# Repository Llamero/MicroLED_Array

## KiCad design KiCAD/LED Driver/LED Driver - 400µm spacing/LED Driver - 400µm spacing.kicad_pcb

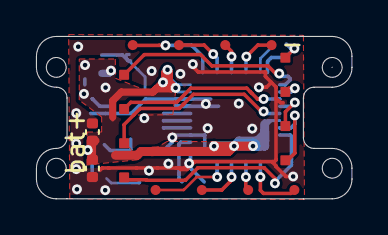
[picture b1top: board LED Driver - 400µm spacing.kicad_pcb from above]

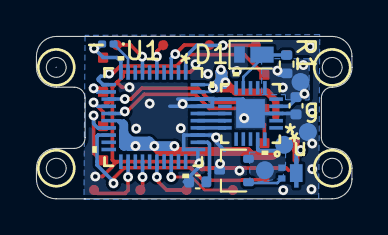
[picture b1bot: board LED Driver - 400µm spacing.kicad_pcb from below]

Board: 2 copper layers, 17.5 x 9.0 mm, 17 parts (15 on the bottom side), 12 nets.

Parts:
BT1: LiPo Cell; LPM0940
C1, C2, C3, C4: 1µF; C_0402_1005Metric
D1: D_Photo; DIO_VEMD4110X01
D2: LED; LED_0201_0603Metric
H1, H2, H3, H4: MountingHole; M1 hole
Q1: Q_NMOS_GSD; SOT-323_SC-70 - thin
R1: 1M; R_0402_1005Metric
TP2: UPDI Pogo Pads; 1mm pad x4
U1: LP5868TRKPR; VQFN40-RKP_TEX
U2: ATtiny3226
U3: XC61GC3002HR-G; XC61G_USP-3_TOR

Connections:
+BATT: C1.1, C3.2, C4.2, R1.1, TP2.3, U1.16 (VLED), U1.39 (VIO_EN), U1.40 (VCC), U2.4 (Vcc), U3.3 (VIN)
-BATT: Q1.2 (S), TP2.4, U3.1 (VSS)
/Col1: D2.2 (A), U1.10 (SW0)
/Photodiode: D1.1 (K), R1.2, U2.9 (4/PB5)
/SCL: U1.35 (SCL_SCK), U2.14 (PB0/9~)
/SDA: U1.36 (SDA_MOSI), U2.13 (8~/PB1)
/UPDI: TP2.2, U2.19 (PA0/17)
/Vsync: U1.34 (VSYNC), U2.15 (PC0/10)
GND: C1.2, C2.2, C3.1, C4.1, D1.2 (A), Q1.3 (D), TP2.1, U1.31 (AGND), U1.33 (IFS), U1.37 (ADDR0_MISO), U1.38 (ADDR1_SS), U2.3 (Gnd), U2.11 (6/PB3), U2.21 (Epad)
unnamed: D2.1 (K), U1.9 (CS8)
unnamed: Q1.1 (G), U3.2 (VOUT)
unnamed: C2.1, U1.32 (VCAP)

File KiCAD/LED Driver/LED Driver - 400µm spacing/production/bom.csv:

Designator,Footprint,Quantity,Value,LCSC Part #
BT1,LPM0940,1,LiPo Cell,
"C1, C2, C3, C4",0402,4,1µF,
D1,DIO_VEMD4110X01,1,D_Photo,
D2,0201,1,LED,
Q1,SOT-323_SC-70 - thin,1,Q_NMOS_GSD,
R1,0402,1,1M,
TP2,1mm pad x4,1,UPDI Pogo Pads,
U1,VQFN40-RKP_TEX,1,LP5868TRKPR,
U2,ATtiny3226,1,ATtiny3226,
U3,XC61G_USP-3_TOR,1,XC61GC3002HR-G,

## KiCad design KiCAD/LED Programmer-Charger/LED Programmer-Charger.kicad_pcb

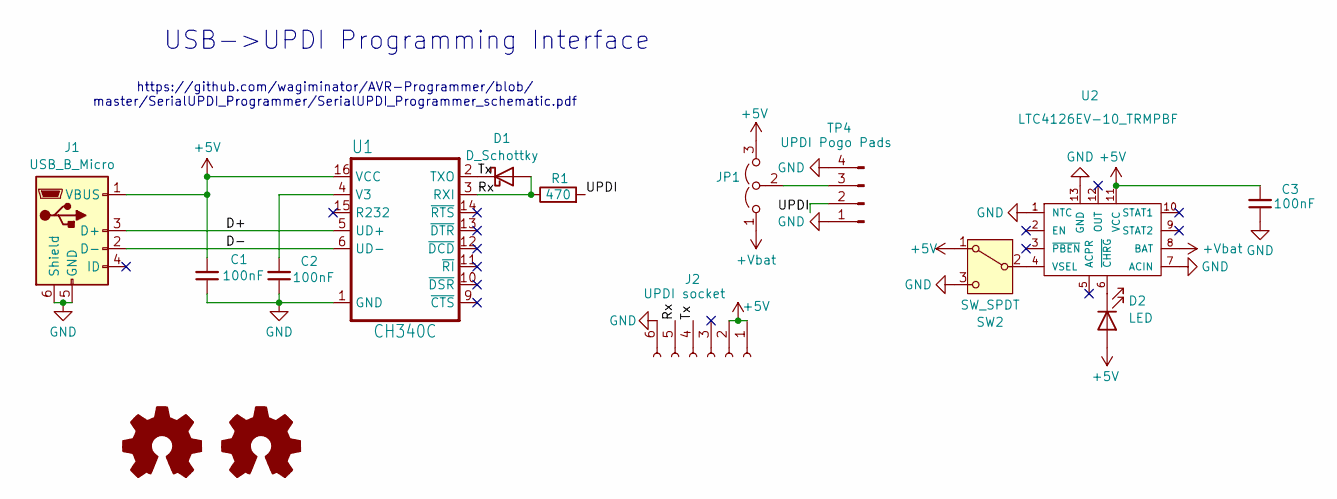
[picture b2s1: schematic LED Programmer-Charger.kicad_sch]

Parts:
C1, C2, C3: 100nF; C_0805_2012Metric; Part MT21B104K500CT
D1: D_Schottky; D_SOD-323; Part CUS10S30,H3F
D2: LED; LED_0603_1608Metric; Part LTST-C170KRKT
J1: USB_B_Micro; CUI_UJ2-MIBH-G-SMT-TR; Part UJ2-MIBH-G-SMT-TR
J2: UPDI socket; PinSocket_1x06_P2.54mm_Vertical_SMD_Pin1Right; Part NPTC061KFXC-RC
JP1: Jumper_3_Open; SolderJumper-3_P2.0mm_Open_TrianglePad1.0x1.5mm
R1: 470; R_0805_2012Metric; Part RP0805FRE07470RL
SW2: SW_SPDT; CL-SB-12B-01_NDC; Part CL-SB-12B-01T
SYM1: Logo_Open_Hardware_Small; CC-BY-SA Symbol
SYM2: Logo_Open_Hardware_Small; OSHW-Logo_5.7x6mm_SilkScreen
TP4: UPDI Pogo Pads; 1mm pad x4; Part 0985-0-15-20-71-14-11-0
U1: CH340C; SOP-16_3.9x9.9mm_P1.27mm; Part B0BK991VVV
U2: LTC4126EV-10_TRMPBF; LTC4126-10; Part LTC4126EV-10#TRMPBF

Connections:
+5V: C1.2, C3.2, D2.2 (A), J1.1 (VBUS), J2.1, J2.2, JP1.3 (B), SW2.1 (A), U1.16 (VCC), U2.11 (VCC)
+Vbat: JP1.1 (A), U2.8 (BAT)
/D+: J1.3 (D+), U1.5 (UD+)
/D-: J1.2 (D-), U1.6 (UD-)
/Rx: D1.2 (A), J2.5, R1.1, U1.3 (RXI)
/Tx: D1.1 (K), J2.4, U1.2 (TXO)
/UPDI: R1.2, TP4.2
GND: C1.1, C2.1, C3.1, J1.5 (GND), J1.6 (Shield), J2.6, SW2.3 (C), TP4.1, TP4.4, U1.1 (GND), U2.1 (NTC), U2.7 (ACIN), U2.13 (GND)
unnamed: D2.1 (K), U2.6 (~CHRG)
unnamed: JP1.2 (C), TP4.3
unnamed: SW2.2 (B), U2.4 (VSEL)
unnamed: C2.2, U1.4 (V3)

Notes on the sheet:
USB->UPDI Programming Interface
https://github.com/wagiminator/AVR-Programmer/blob/ master/SerialUPDI_Programmer/SerialUPDI_Programmer_schematic.pdf

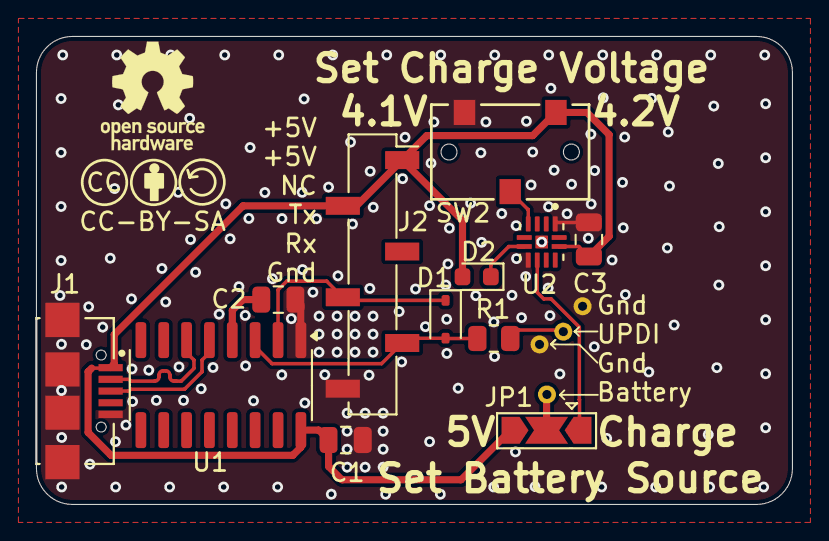
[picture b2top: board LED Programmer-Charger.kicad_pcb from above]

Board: 2 copper layers, 42.0 x 26.0 mm, 15 parts (0 on the bottom side), 12 nets.

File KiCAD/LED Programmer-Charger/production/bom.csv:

Designator,Footprint,Quantity,Value,LCSC Part #
"C1, C2, C3",0805,3,100nF,
D1,D_SOD-323,1,D_Schottky,
D2,0603,1,LED,
J1,CUI_UJ2-MIBH-G-SMT-TR,1,USB_B_Micro,
J2,PinSocket_1x06_P2.54mm_Vertical_SMD_Pin1Right,1,UPDI socket,
R1,0805,1,470,
SW2,CL-SB-12B-01_NDC,1,SW_SPDT,
TP4,1mm pad x4,1,UPDI Pogo Pads,
U1,SOP-16_3.9x9.9mm_P1.27mm,1,CH340C,
U2,LTC4126-10,1,LTC4126EV-10_TRMPBF,

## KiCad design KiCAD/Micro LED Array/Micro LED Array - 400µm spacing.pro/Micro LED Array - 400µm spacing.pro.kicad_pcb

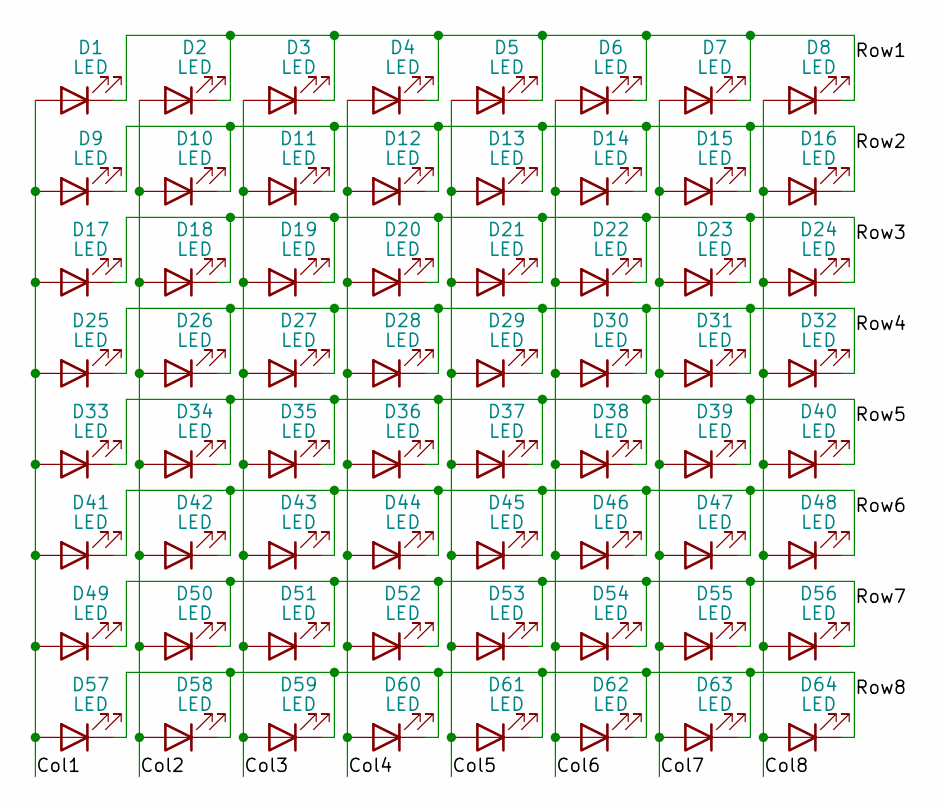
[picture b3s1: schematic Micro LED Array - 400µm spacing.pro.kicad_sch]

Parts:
D1, D2, D3, D4, D5, D6, D7, D8, D9, D10, D11, D12, D13, D14, D15, D16, D17, D18, D19, D20, D21, D22, D23, D24, D25, D26, D27, D28, D29, D30, D31, D32, D33, D34, D35, D36, D37, D38, D39, D40, D41, D42, D43, D44, D45, D46, D47, D48, D49, D50, D51, D52, D53, D54, D55, D56, D57, D58, D59, D60, D61, D62, D63, D64: LED; LED_APG0603SEC-E-TT_KNB - with via; Part LTST-FC03AD-5A

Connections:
/Col1: D1.2 (A), D9.2 (A), D17.2 (A), D25.2 (A), D33.2 (A), D41.2 (A), D49.2 (A), D57.2 (A)
/Col2: D2.2 (A), D10.2 (A), D18.2 (A), D26.2 (A), D34.2 (A), D42.2 (A), D50.2 (A), D58.2 (A)
/Col3: D3.2 (A), D11.2 (A), D19.2 (A), D27.2 (A), D35.2 (A), D43.2 (A), D51.2 (A), D59.2 (A)
/Col4: D4.2 (A), D12.2 (A), D20.2 (A), D28.2 (A), D36.2 (A), D44.2 (A), D52.2 (A), D60.2 (A)
/Col5: D5.2 (A), D13.2 (A), D21.2 (A), D29.2 (A), D37.2 (A), D45.2 (A), D53.2 (A), D61.2 (A)
/Col6: D6.2 (A), D14.2 (A), D22.2 (A), D30.2 (A), D38.2 (A), D46.2 (A), D54.2 (A), D62.2 (A)
/Col7: D7.2 (A), D15.2 (A), D23.2 (A), D31.2 (A), D39.2 (A), D47.2 (A), D55.2 (A), D63.2 (A)
/Col8: D8.2 (A), D16.2 (A), D24.2 (A), D32.2 (A), D40.2 (A), D48.2 (A), D56.2 (A), D64.2 (A)
/Row1: D1.1 (K), D2.1 (K), D3.1 (K), D4.1 (K), D5.1 (K), D6.1 (K), D7.1 (K), D8.1 (K)
/Row2: D9.1 (K), D10.1 (K), D11.1 (K), D12.1 (K), D13.1 (K), D14.1 (K), D15.1 (K), D16.1 (K)
/Row3: D17.1 (K), D18.1 (K), D19.1 (K), D20.1 (K), D21.1 (K), D22.1 (K), D23.1 (K), D24.1 (K)
/Row4: D25.1 (K), D26.1 (K), D27.1 (K), D28.1 (K), D29.1 (K), D30.1 (K), D31.1 (K), D32.1 (K)
/Row5: D33.1 (K), D34.1 (K), D35.1 (K), D36.1 (K), D37.1 (K), D38.1 (K), D39.1 (K), D40.1 (K)
/Row6: D41.1 (K), D42.1 (K), D43.1 (K), D44.1 (K), D45.1 (K), D46.1 (K), D47.1 (K), D48.1 (K)
/Row7: D49.1 (K), D50.1 (K), D51.1 (K), D52.1 (K), D53.1 (K), D54.1 (K), D55.1 (K), D56.1 (K)
/Row8: D57.1 (K), D58.1 (K), D59.1 (K), D60.1 (K), D61.1 (K), D62.1 (K), D63.1 (K), D64.1 (K)

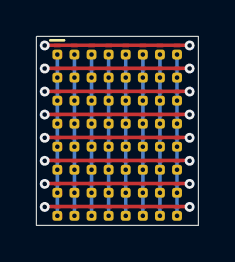
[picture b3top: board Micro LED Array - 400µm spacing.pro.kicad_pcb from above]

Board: 2 copper layers, 9.0 x 10.5 mm, 64 parts (0 on the bottom side), 16 nets.

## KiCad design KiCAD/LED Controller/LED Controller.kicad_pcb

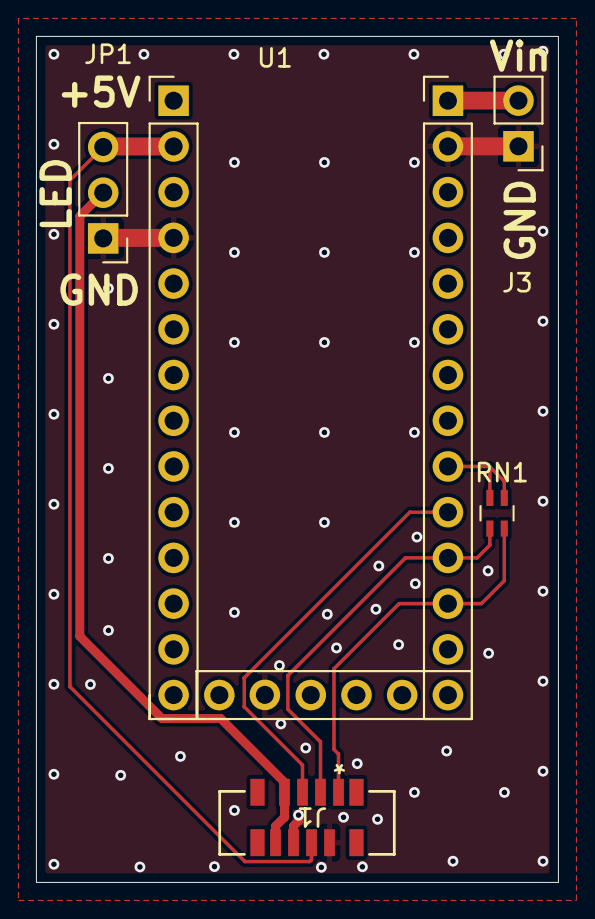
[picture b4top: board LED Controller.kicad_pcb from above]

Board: 2 copper layers, 29.0 x 47.0 mm, 5 parts (0 on the bottom side), 8 nets.

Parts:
J1: 0525590870; CON_525590870_MOL - 8x ribbon vert
J3: Conn_01x02_Pin; PinHeader_1x02_P2.54mm_Vertical
JP1: Jumper_3_Open; PinHeader_1x03_P2.54mm_Vertical
RN1: R_Pack02; R_Array_Concave_2x0603
U1: Itsy_Bitsy_32u4; Itsy Bitsy 32u4

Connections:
+5V: J1.4, JP1.3 (B), U1.2 (5V)
/12V: J3.2, U1.33 (VBat)
/SCL: J1.3, RN1.3 (R2.2), U1.23 (~3_SCL)
/SDA: J1.1, RN1.4 (R1.2), U1.22 (2_SDA)
/VLED: J1.7, J1.8, JP1.2 (C)
/Vsync: J1.5, U1.24 (~5)
GND: J1.2, J1.6, J3.1, JP1.1 (A), U1.4 (GND), U1.16 (Gnd), U1.32 (Gnd)
unnamed: RN1.1 (R1.1), RN1.2 (R2.1), U1.25 (7)

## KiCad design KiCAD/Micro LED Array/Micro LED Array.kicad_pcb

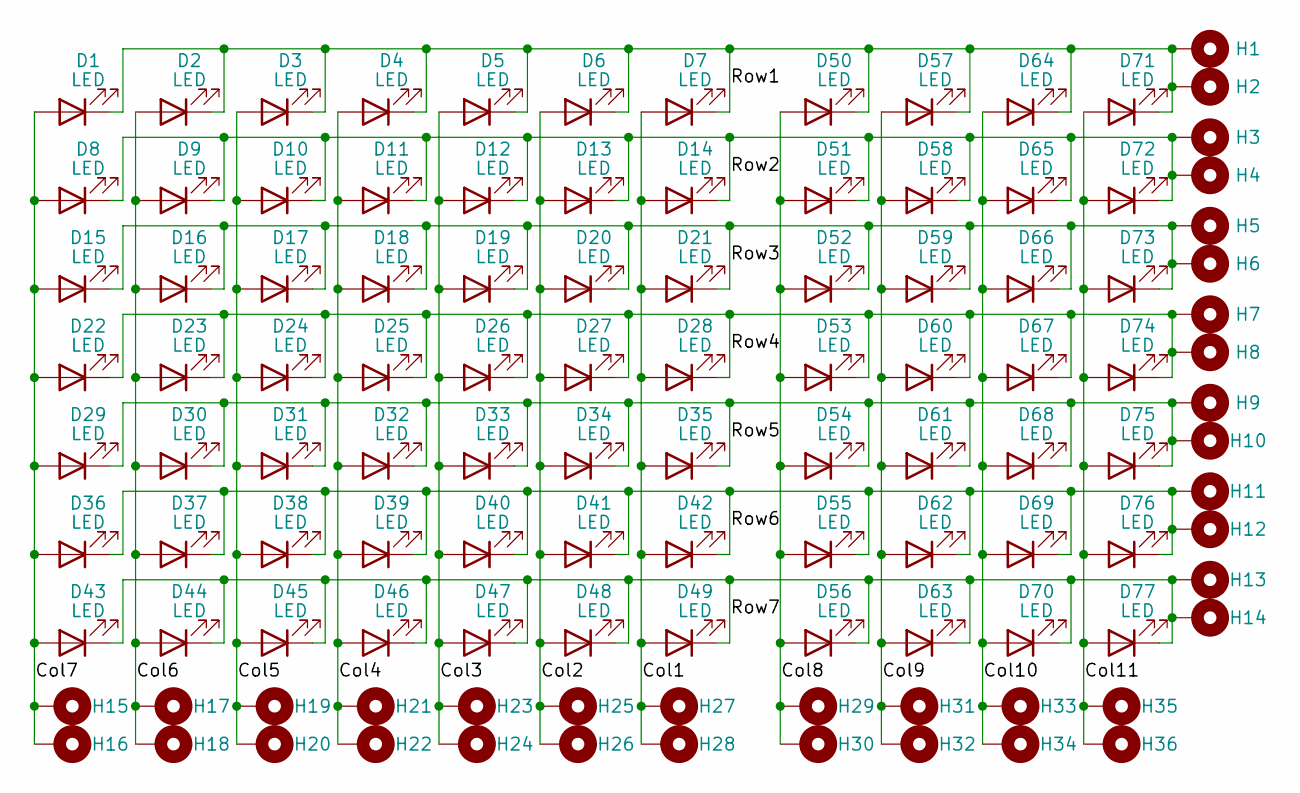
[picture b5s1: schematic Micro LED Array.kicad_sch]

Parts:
D1, D2, D3, D4, D5, D6, D7, D8, D9, D10, D11, D12, D13, D14, D15, D16, D17, D18, D19, D20, D21, D22, D23, D24, D25, D26, D27, D28, D29, D30, D31, D32, D33, D34, D35, D36, D37, D38, D39, D40, D41, D42, D43, D44, D45, D46, D47, D48, D49, D50, D51, D52, D53, D54, D55, D56, D57, D58, D59, D60, D61, D62, D63, D64, D65, D66, D67, D68, D69, D70, D71, D72, D73, D74, D75, D76, D77: LED; LED_APG0603SEC-E-TT_KNB - with via; Part APG0603SEC-E-TT
H1, H2, H3, H4, H5, H6, H7, H8, H9, H10, H11, H12, H13, H14, H15, H16, H17, H18, H19, H20, H21, H22, H23, H24, H25, H26, H27, H28, H29, H30, H31, H32, H33, H34, H35, H36: Via Pad; Column Via

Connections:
/Col1: D7.2 (A), D14.2 (A), D21.2 (A), D28.2 (A), D35.2 (A), D42.2 (A), D49.2 (A), H27.1, H28.1
/Col2: D6.2 (A), D13.2 (A), D20.2 (A), D27.2 (A), D34.2 (A), D41.2 (A), D48.2 (A), H25.1, H26.1
/Col3: D5.2 (A), D12.2 (A), D19.2 (A), D26.2 (A), D33.2 (A), D40.2 (A), D47.2 (A), H23.1, H24.1
/Col4: D4.2 (A), D11.2 (A), D18.2 (A), D25.2 (A), D32.2 (A), D39.2 (A), D46.2 (A), H21.1, H22.1
/Col5: D3.2 (A), D10.2 (A), D17.2 (A), D24.2 (A), D31.2 (A), D38.2 (A), D45.2 (A), H19.1, H20.1
/Col6: D2.2 (A), D9.2 (A), D16.2 (A), D23.2 (A), D30.2 (A), D37.2 (A), D44.2 (A), H17.1, H18.1
/Col7: D1.2 (A), D8.2 (A), D15.2 (A), D22.2 (A), D29.2 (A), D36.2 (A), D43.2 (A), H15.1, H16.1
/Col8: D50.2 (A), D51.2 (A), D52.2 (A), D53.2 (A), D54.2 (A), D55.2 (A), D56.2 (A), H29.1, H30.1
/Col9: D57.2 (A), D58.2 (A), D59.2 (A), D60.2 (A), D61.2 (A), D62.2 (A), D63.2 (A), H31.1, H32.1
/Col10: D64.2 (A), D65.2 (A), D66.2 (A), D67.2 (A), D68.2 (A), D69.2 (A), D70.2 (A), H33.1, H34.1
/Col11: D71.2 (A), D72.2 (A), D73.2 (A), D74.2 (A), D75.2 (A), D76.2 (A), D77.2 (A), H35.1, H36.1
/Row1: D1.1 (K), D2.1 (K), D3.1 (K), D4.1 (K), D5.1 (K), D6.1 (K), D7.1 (K), D50.1 (K), D57.1 (K), D64.1 (K), D71.1 (K), H1.1, H2.1
/Row2: D8.1 (K), D9.1 (K), D10.1 (K), D11.1 (K), D12.1 (K), D13.1 (K), D14.1 (K), D51.1 (K), D58.1 (K), D65.1 (K), D72.1 (K), H3.1, H4.1
/Row3: D15.1 (K), D16.1 (K), D17.1 (K), D18.1 (K), D19.1 (K), D20.1 (K), D21.1 (K), D52.1 (K), D59.1 (K), D66.1 (K), D73.1 (K), H5.1, H6.1
/Row4: D22.1 (K), D23.1 (K), D24.1 (K), D25.1 (K), D26.1 (K), D27.1 (K), D28.1 (K), D53.1 (K), D60.1 (K), D67.1 (K), D74.1 (K), H7.1, H8.1
/Row5: D29.1 (K), D30.1 (K), D31.1 (K), D32.1 (K), D33.1 (K), D34.1 (K), D35.1 (K), D54.1 (K), D61.1 (K), D68.1 (K), D75.1 (K), H9.1, H10.1
/Row6: D36.1 (K), D37.1 (K), D38.1 (K), D39.1 (K), D40.1 (K), D41.1 (K), D42.1 (K), D55.1 (K), D62.1 (K), D69.1 (K), D76.1 (K), H11.1, H12.1
/Row7: D43.1 (K), D44.1 (K), D45.1 (K), D46.1 (K), D47.1 (K), D48.1 (K), D49.1 (K), D56.1 (K), D63.1 (K), D70.1 (K), D77.1 (K), H13.1, H14.1

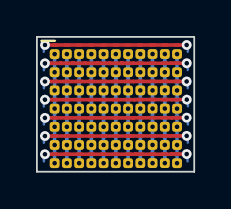
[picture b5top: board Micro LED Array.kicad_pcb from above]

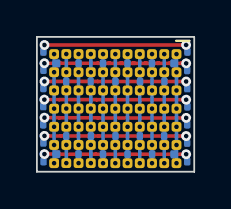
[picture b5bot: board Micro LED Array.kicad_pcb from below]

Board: 2 copper layers, 8.7 x 7.5 mm, 113 parts (36 on the bottom side), 18 nets.

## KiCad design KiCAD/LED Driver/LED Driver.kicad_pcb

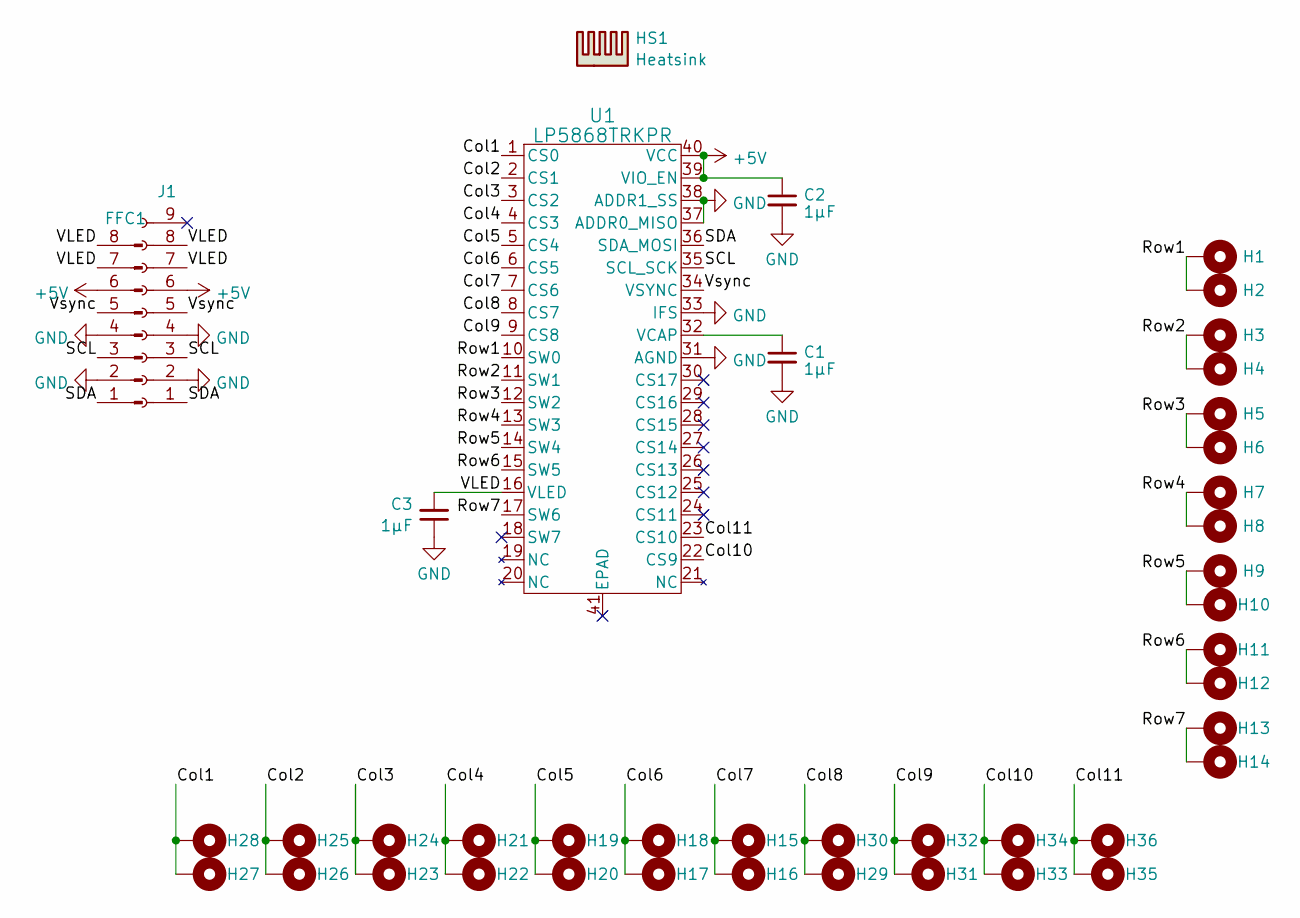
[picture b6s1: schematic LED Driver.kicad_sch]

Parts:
C1, C2, C3: 1µF; C_0402_1005Metric; Part CL05A105KA5NQNC
FFC1: FFC; Part 0151660093
H1, H2, H3, H4, H5, H6, H7, H8, H9, H10, H11, H12, H13, H14, H15, H16, H17, H18, H19, H20, H21, H22, H23, H24, H25, H26, H27, H28, H29, H30, H31, H32, H33, H34, H35, H36: Via Pad; Column Via
HS1: Heatsink; heatsink; Part V2016B
J1: 0525590870; CON_525590870_MOL - 8x ribbon vert; Part 0525590870
U1: LP5868TRKPR; VQFN40-RKP_TEX; Part LP5868TRKPR

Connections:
+5V: C2.1, FFC1.6, J1.6, U1.39 (VIO_EN), U1.40 (VCC)
/Col1: H27.1, H28.1, U1.1 (CS0)
/Col2: H25.1, H26.1, U1.2 (CS1)
/Col3: H23.1, H24.1, U1.3 (CS2)
/Col4: H21.1, H22.1, U1.4 (CS3)
/Col5: H19.1, H20.1, U1.5 (CS4)
/Col6: H17.1, H18.1, U1.6 (CS5)
/Col7: H15.1, H16.1, U1.7 (CS6)
/Col8: H29.1, H30.1, U1.8 (CS7)
/Col9: H31.1, H32.1, U1.9 (CS8)
/Col10: H33.1, H34.1, U1.22 (CS9)
/Col11: H35.1, H36.1, U1.23 (CS10)
/Row1: H1.1, H2.1, U1.10 (SW0)
/Row2: H3.1, H4.1, U1.11 (SW1)
/Row3: H5.1, H6.1, U1.12 (SW2)
/Row4: H7.1, H8.1, U1.13 (SW3)
/Row5: H9.1, H10.1, U1.14 (SW4)
/Row6: H11.1, H12.1, U1.15 (SW5)
/Row7: H13.1, H14.1, U1.17 (SW6)
/SCL: FFC1.3, J1.3, U1.35 (SCL_SCK)
/SDA: FFC1.1, J1.1, U1.36 (SDA_MOSI)
/VLED: C3.2, FFC1.7, FFC1.8, J1.7, J1.8, U1.16 (VLED)
/Vsync: FFC1.5, J1.5, U1.34 (VSYNC)
GND: C1.2, C2.2, C3.1, FFC1.2, FFC1.4, J1.2, J1.4, U1.31 (AGND), U1.33 (IFS), U1.37 (ADDR0_MISO), U1.38 (ADDR1_SS)
unnamed: C1.1, U1.32 (VCAP)

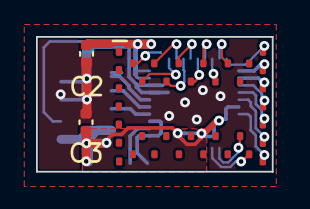
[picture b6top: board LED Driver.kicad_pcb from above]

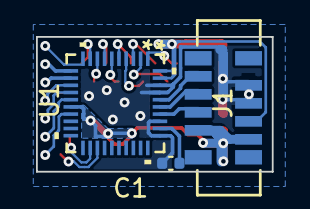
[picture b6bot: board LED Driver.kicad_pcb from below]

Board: 2 copper layers, 13.1 x 7.5 mm, 42 parts (4 on the bottom side), 25 nets.

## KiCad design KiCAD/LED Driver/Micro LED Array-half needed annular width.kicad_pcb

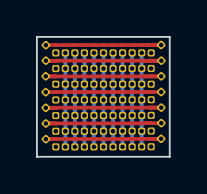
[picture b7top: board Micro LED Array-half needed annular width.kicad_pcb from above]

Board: 2 copper layers, 7.4 x 6.7 mm, 91 parts (0 on the bottom side), 18 nets.

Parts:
D1, D2, D3, D4, D5, D6, D7, D8, D9, D10, D11, D12, D13, D14, D15, D16, D17, D18, D19, D20, D21, D22, D23, D24, D25, D26, D27, D28, D29, D30, D31, D32, D33, D34, D35, D36, D37, D38, D39, D40, D41, D42, D43, D44, D45, D46, D47, D48, D49, D50, D51, D52, D53, D54, D55, D56, D57, D58, D59, D60, D61, D62, D63, D64, D65, D66, D67, D68, D69, D70, D71, D72, D73, D74, D75, D76, D77: LED; LED_APG0603SEC-E-TT_KNB - with via
H1, H2, H3, H4, H5, H6, H7, H8, H9, H10, H11, H12, H13, H14: Via Pad; Row Via

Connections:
/Col1: D1.2 (A), D8.2 (A), D15.2 (A), D22.2 (A), D29.2 (A), D36.2 (A), D43.2 (A)
/Col2: D2.2 (A), D9.2 (A), D16.2 (A), D23.2 (A), D30.2 (A), D37.2 (A), D44.2 (A)
/Col3: D3.2 (A), D10.2 (A), D17.2 (A), D24.2 (A), D31.2 (A), D38.2 (A), D45.2 (A)
/Col4: D4.2 (A), D11.2 (A), D18.2 (A), D25.2 (A), D32.2 (A), D39.2 (A), D46.2 (A)
/Col5: D5.2 (A), D12.2 (A), D19.2 (A), D26.2 (A), D33.2 (A), D40.2 (A), D47.2 (A)
/Col6: D6.2 (A), D13.2 (A), D20.2 (A), D27.2 (A), D34.2 (A), D41.2 (A), D48.2 (A)
/Col7: D7.2 (A), D14.2 (A), D21.2 (A), D28.2 (A), D35.2 (A), D42.2 (A), D49.2 (A)
/Col8: D50.2 (A), D51.2 (A), D52.2 (A), D53.2 (A), D54.2 (A), D55.2 (A), D56.2 (A)
/Col9: D57.2 (A), D58.2 (A), D59.2 (A), D60.2 (A), D61.2 (A), D62.2 (A), D63.2 (A)
/Col10: D64.2 (A), D65.2 (A), D66.2 (A), D67.2 (A), D68.2 (A), D69.2 (A), D70.2 (A)
/Col11: D71.2 (A), D72.2 (A), D73.2 (A), D74.2 (A), D75.2 (A), D76.2 (A), D77.2 (A)
/Row1: D1.1 (K), D2.1 (K), D3.1 (K), D4.1 (K), D5.1 (K), D6.1 (K), D7.1 (K), D50.1 (K), D57.1 (K), D64.1 (K), D71.1 (K), H1.1, H2.1
/Row2: D8.1 (K), D9.1 (K), D10.1 (K), D11.1 (K), D12.1 (K), D13.1 (K), D14.1 (K), D51.1 (K), D58.1 (K), D65.1 (K), D72.1 (K), H3.1, H4.1
/Row3: D15.1 (K), D16.1 (K), D17.1 (K), D18.1 (K), D19.1 (K), D20.1 (K), D21.1 (K), D52.1 (K), D59.1 (K), D66.1 (K), D73.1 (K), H5.1, H6.1
/Row4: D22.1 (K), D23.1 (K), D24.1 (K), D25.1 (K), D26.1 (K), D27.1 (K), D28.1 (K), D53.1 (K), D60.1 (K), D67.1 (K), D74.1 (K), H7.1, H8.1
/Row5: D29.1 (K), D30.1 (K), D31.1 (K), D32.1 (K), D33.1 (K), D34.1 (K), D35.1 (K), D54.1 (K), D61.1 (K), D68.1 (K), D75.1 (K), H9.1, H10.1
/Row6: D36.1 (K), D37.1 (K), D38.1 (K), D39.1 (K), D40.1 (K), D41.1 (K), D42.1 (K), D55.1 (K), D62.1 (K), D69.1 (K), D76.1 (K), H11.1, H12.1
/Row7: D43.1 (K), D44.1 (K), D45.1 (K), D46.1 (K), D47.1 (K), D48.1 (K), D49.1 (K), D56.1 (K), D63.1 (K), D70.1 (K), D77.1 (K), H13.1, H14.1

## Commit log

2024-06-08 working draft 7x11
2024-06-18 Working draft
2024-06-21 Add holes for electrodes
2025-04-25 Driver board connected, add interboard fiducials
2025-04-25 test
2025-04-25 Recovering bad merge
2025-04-26 Fix LED array 0201 footprint for centroid file for assembly
2025-04-29 Add 400µm spacing for assembly
2025-04-30 Add controller - move ground
2025-07-08 minor edits
2025-07-11 Add microcontroller
2025-07-15 low-volt cutoff, indicator LED, and mounting bolts added
2025-07-31 Working draft of programmer/charger board
2025-07-31 Build CAD files of assembly
2025-08-01 Remove status pads for charger as DC-DC converter is required
2025-08-04 Move bolts 1 mm
2025-08-16 Add demo code showing position control
2025-08-29 Add demo
2025-08-29 IR LED meter demo added
2025-09-05 NEC-ish encoding implemented for serial transmission of data
2025-09-06 Added code for powering off peripherals and sleeping when able
2025-09-06 Clear interrupt flag so device goes back to standby after message
2025-09-08 Standby current reduced to 122 µA + fixed bug blocking return to sleep
2025-09-08 Clean up Python demo code
2025-09-13 9 µA sleep with 2s IR pulse wake
2025-09-23 Increase sensitivity and re-calibrate photodiode each time device wakes
